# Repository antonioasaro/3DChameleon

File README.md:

Remix of the (very clever) 3DChamelon design for multi-colour 3D printing.

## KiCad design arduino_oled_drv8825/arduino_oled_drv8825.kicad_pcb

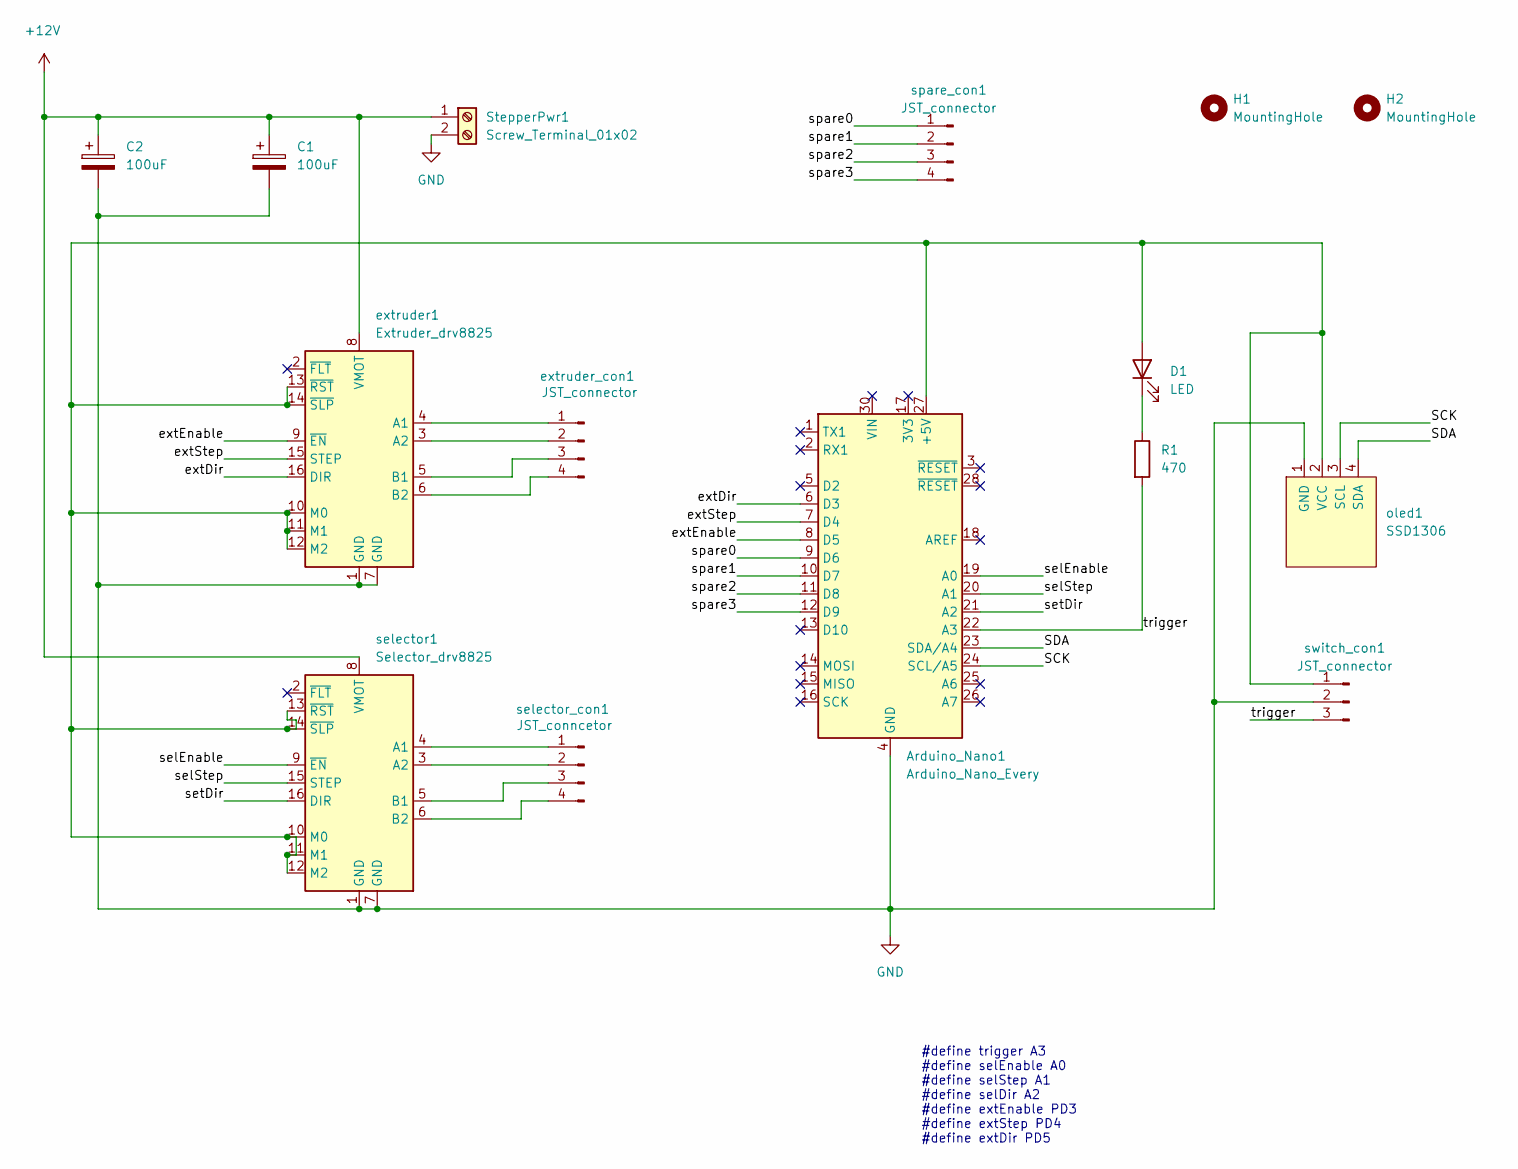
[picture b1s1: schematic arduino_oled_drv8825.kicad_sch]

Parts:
Arduino_Nano1: Arduino_Nano_Every
C1: 100uF; CP_Radial_D5.0mm_P2.50mm
C2: 100uF; CP_Radial_D5.0mm_P2.00mm
D1: LED; LED_D3.0mm
H1, H2: MountingHole; MountingHole_3.2mm_M3
R1: 470; R_Axial_DIN0204_L3.6mm_D1.6mm_P2.54mm_Vertical
StepperPwr1: Screw_Terminal_01x02; TerminalBlock_Phoenix_MKDS-1,5-2-5.08_1x02_P5.08mm_Horizont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
extruder1: Extruder_drv8825; Pololu_Breakout-16_15.2x20.3mm
extruder_con1: JST_connector; JST_EH_B4B-EH-A_1x04_P2.50mm_Vertical
oled1: SSD1306; 128x64OLED
selector1: Selector_drv8825; Pololu_Breakout-16_15.2x20.3mm
selector_con1: JST_conncetor; JST_EH_B4B-EH-A_1x04_P2.50mm_Vertical
spare_con1: JST_connector; JST_EH_B4B-EH-A_1x04_P2.50mm_Vertical
switch_con1: JST_connector; JST_EH_B3B-EH-A_1x03_P2.50mm_Vertical

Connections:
+12V: C1.1, C2.1, StepperPwr1.1, extruder1.8 (VMOT), selector1.8 (VMOT)
/SCK: Arduino_Nano1.24 (SCL/A5), oled1.3 (SCL)
/SDA: Arduino_Nano1.23 (SDA/A4), oled1.4 (SDA)
/extDir: Arduino_Nano1.6 (D3), extruder1.16 (DIR)
/extEnable: Arduino_Nano1.8 (D5), extruder1.9 (~EN)
/extStep: Arduino_Nano1.7 (D4), extruder1.15 (STEP)
/selEnable: Arduino_Nano1.19 (A0), selector1.9 (~EN)
/selStep: Arduino_Nano1.20 (A1), selector1.15 (STEP)
/setDir: Arduino_Nano1.21 (A2), selector1.16 (DIR)
/spare0: Arduino_Nano1.9 (D6), spare_con1.1
/spare1: Arduino_Nano1.10 (D7), spare_con1.2
/spare2: Arduino_Nano1.11 (D8), spare_con1.3
/spare3: Arduino_Nano1.12 (D9), spare_con1.4
/trigger: Arduino_Nano1.22 (A3), R1.2, switch_con1.3
GND: Arduino_Nano1.4 (GND), Arduino_Nano1.29 (GND), C1.2, C2.2, StepperPwr1.2, extruder1.1 (GND), extruder1.7 (GND), oled1.1 (GND), selector1.1 (GND), selector1.7 (GND), switch_con1.2
unnamed: Arduino_Nano1.27 (+5V), D1.2 (A), extruder1.10 (M0), extruder1.11 (M1), extruder1.12 (M2), extruder1.13 (~RST), extruder1.14 (~SLP), oled1.2 (VCC), selector1.10 (M0), selector1.11 (M1), selector1.12 (M2), selector1.13 (~RST), selector1.14 (~SLP), switch_con1.1
unnamed: D1.1 (K), R1.1
unnamed: extruder1.4 (A1), extruder_con1.1
unnamed: extruder1.3 (A2), extruder_con1.2
unnamed: extruder1.5 (B1), extruder_con1.3
unnamed: extruder1.6 (B2), extruder_con1.4
unnamed: selector1.4 (A1), selector_con1.1
unnamed: selector1.3 (A2), selector_con1.2
unnamed: selector1.5 (B1), selector_con1.3
unnamed: selector1.6 (B2), selector_con1.4

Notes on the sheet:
#define trigger A3 #define selEnable A0 #define selStep A1 #define selDir A2 #define extEnable PD3 #define extStep PD4 #define extDir PD5

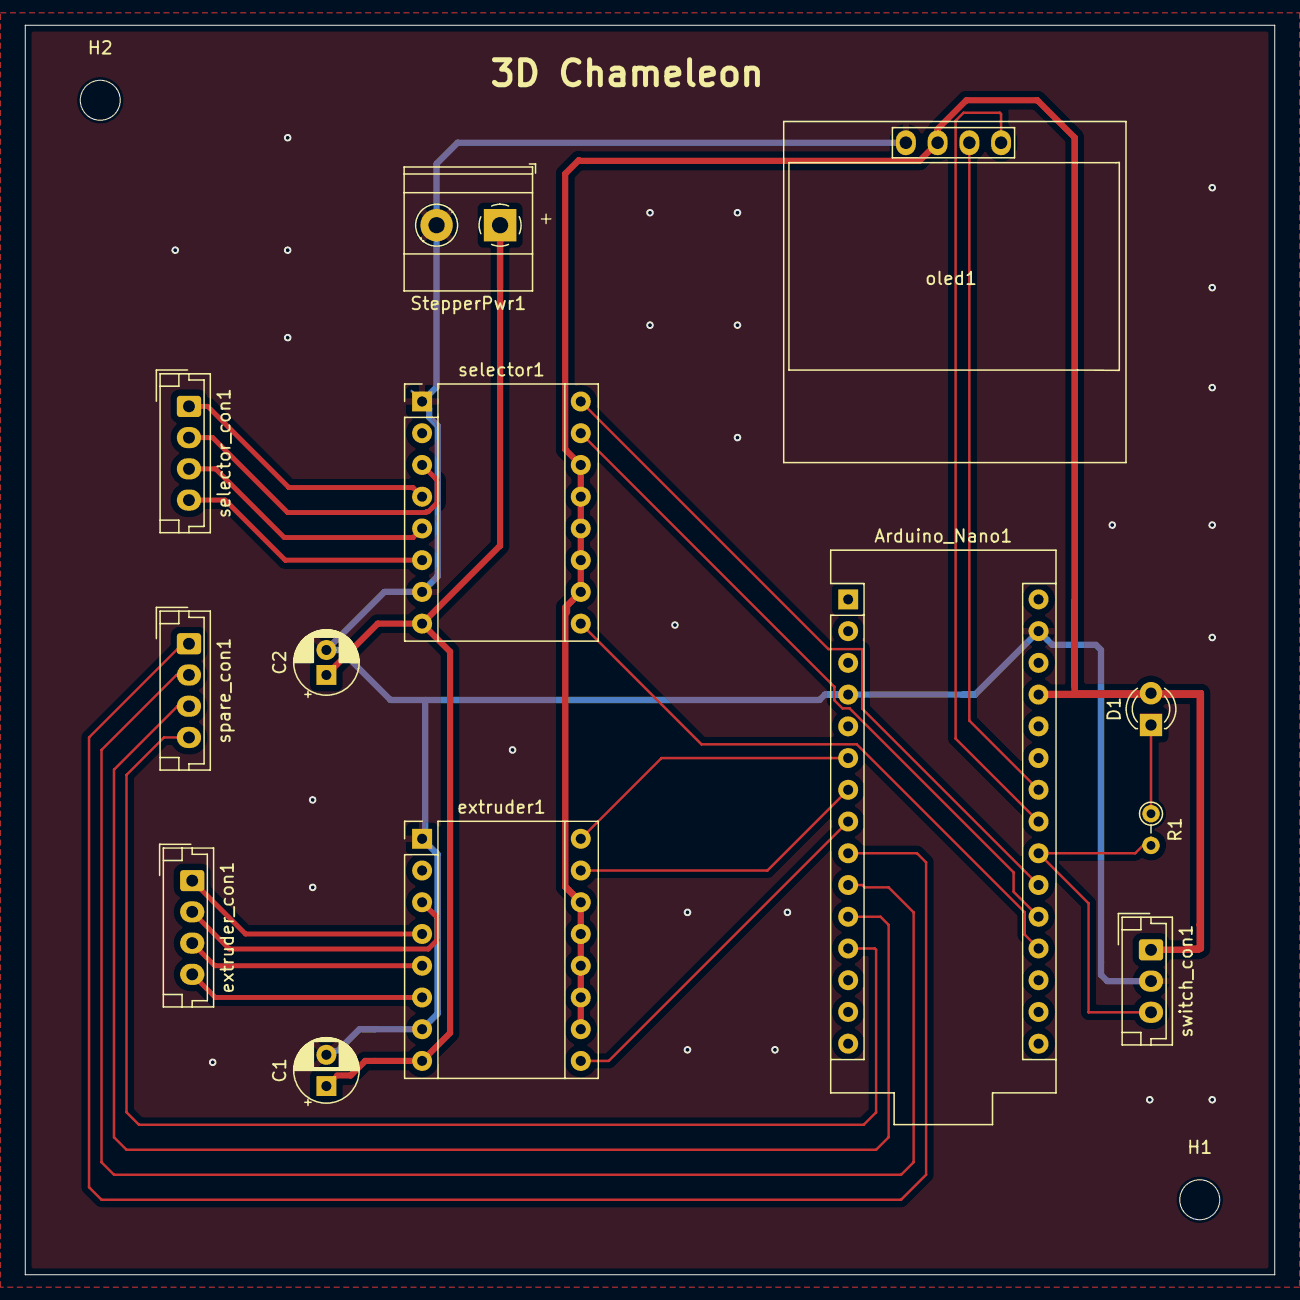
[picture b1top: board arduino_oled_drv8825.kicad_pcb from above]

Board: 2 copper layers, 100.0 x 100.0 mm, 15 parts (0 on the bottom side), 25 nets.

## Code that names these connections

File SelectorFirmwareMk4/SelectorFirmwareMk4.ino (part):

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SX1509 io;                        // Create an SX1509 object to be used throughout

// defines pins numbers - 3D Chameleon Board
#define extEnable PD5
#define extStep PD4
#define extDir PD3

#define selEnable A0
#define selStep A1
#define selDir A2

#define trigger A3
#define s_limit A4
#define filament A5

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  seenCommand = 0;

  // Sets the two pins as Outputs
  pinMode(extEnable, OUTPUT);
  pinMode(extStep, OUTPUT);
  pinMode(extDir, OUTPUT);

  pinMode(selEnable, OUTPUT);
  pinMode(selStep, OUTPUT);
  pinMode(selDir, OUTPUT);

  // set up the button
  pinMode(trigger, INPUT_PULLUP);  // selector

  // a little override here... we're using the two inputs as I2C instead
  pinMode(s_limit, OUTPUT);    
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
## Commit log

2025-02-16 Initial version
2025-02-17 Included cfg files with kilpper macros
2025-02-17 Added STL files
2025-02-17 More STL files
2025-02-23 filament swapping test

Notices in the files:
SelectorFirmwareMk4/SelectorFirmwareMk4.ino:
Copyright 2024 William J. Steele
